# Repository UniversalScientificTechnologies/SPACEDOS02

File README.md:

# SPACEDOS02A - PIN diode dosimeter for manned spacecraft 

SPACEDOS is a miniature and lightweight version of [AIRDOS02](https://github.com/UniversalScientificTechnologies/AIRDOS02) cosmic radiation dosimeter modified for use onboard manned spacecraft.

The device is currently being used onboard ISS. The following pictures show the processed data from the flight. Here is a radiation map, where the [South Atlantic Anomaly](https://en.wikipedia.org/wiki/South_Atlantic_Anomaly) is visible.

The following spectrum is a cumulative sum of all the measured particles during the flight. 

## Technical parameters are as follows:

* Silicon PIN diode detector with 0.22 x 10 x 20 ~ 44 mm³ detection volume
* Measurement environment: atmosphere > 70 kPa
* Measurement endurance: 120 days (4 months of measurement)
* Number of energy channels: 240
* Integration time: Customizable in a wide range from milliseconds to minutes
* Deposited energy range: from 180 keV to 8.5 MeV
* Energy measurement resolution: < 50 keV/channel
* Thermal stability: 1 channel per 12 °C
* Power supply: battery 3.6 V LS 33600
* Power consumption: < 10 mW during measurement, < 120 mW during writing to SD card
* Data storage media: Standard size SDcard, Industry-grade SLC  SD card
* Interface: RS232/UART 3.3V TTL
* Radiation durability: 50 mGy - currently limited by the durability of a storage media
* Dimensions(HxWxL): 60mm x 39mm x 113 mm
* Mass / (including battery): 58/148 g 

## Relevant scientific publications

* [SPACEDOS: AN OPEN-SOURCE PIN DIODE DOSEMETER FOR APPLICATIONS IN SPACE](https://academic.oup.com/rpd/article-abstract/198/9-11/611/6673003?redirectedFrom=fulltext&login=false)
* [SPACEDOS an open-source PIN diode dosimeter for applications in Space](https://indico.ujf.cas.cz/event/2/contributions/27/attachments/25/46/Po-1315-Kakona-774711333.pdf)

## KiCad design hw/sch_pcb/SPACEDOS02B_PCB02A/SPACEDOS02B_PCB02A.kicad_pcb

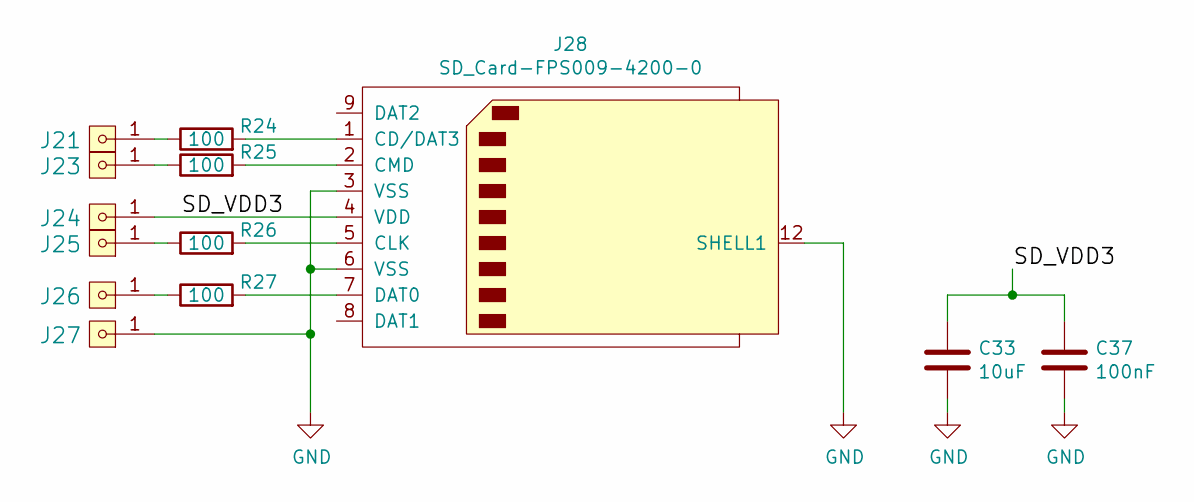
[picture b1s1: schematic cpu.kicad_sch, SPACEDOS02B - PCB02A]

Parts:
C33: 10uF; SMD-0805
C37: 100nF; SMD-0805
J21, J23, J24, J25, J26, J27: HEADER_1x01; Straight_1x01
J28: SD_Card-FPS009-4200-0; FPS009-4200-0
R24, R25, R26, R27: 100; SMD-0805

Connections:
/cpu/SD_VDD3: C33.1, C37.1, J24.1, J28.4 (VDD)
GND: C33.2, C37.2, J27.1, J28.3 (VSS), J28.6 (VSS), J28.12 (SHELL1)
unnamed: J21.1, R24.1
unnamed: J23.1, R25.1
unnamed: J25.1, R26.1
unnamed: J26.1, R27.1
unnamed: J28.1 (CD/DAT3), R24.2
unnamed: J28.2 (CMD), R25.2
unnamed: J28.5 (CLK), R26.2
unnamed: J28.7 (DAT0), R27.2

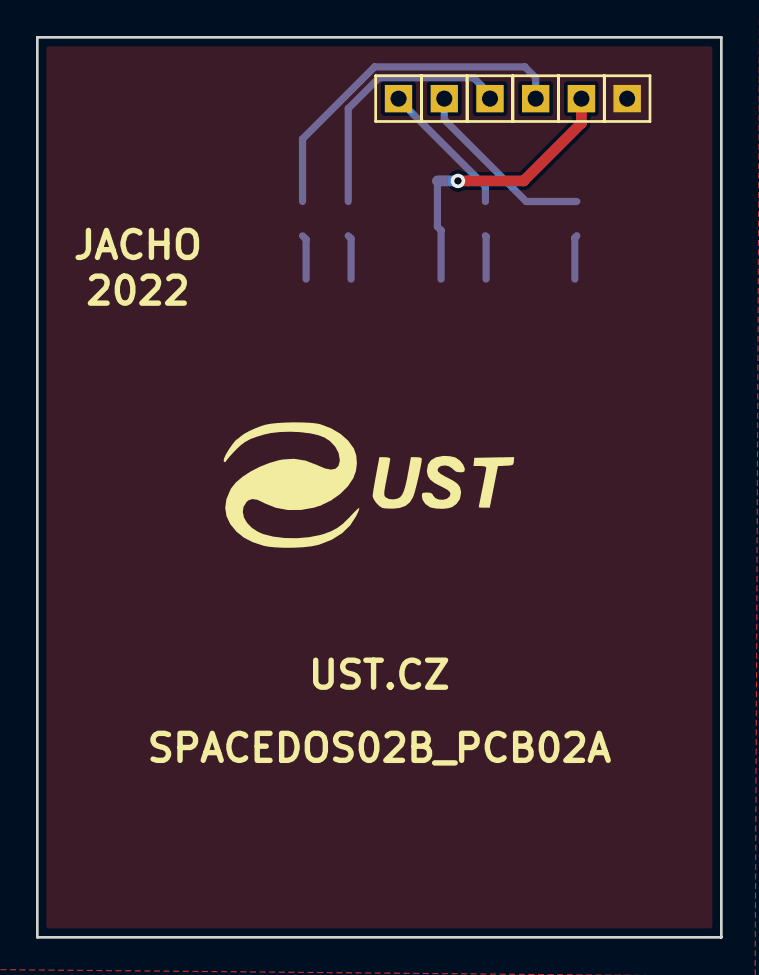
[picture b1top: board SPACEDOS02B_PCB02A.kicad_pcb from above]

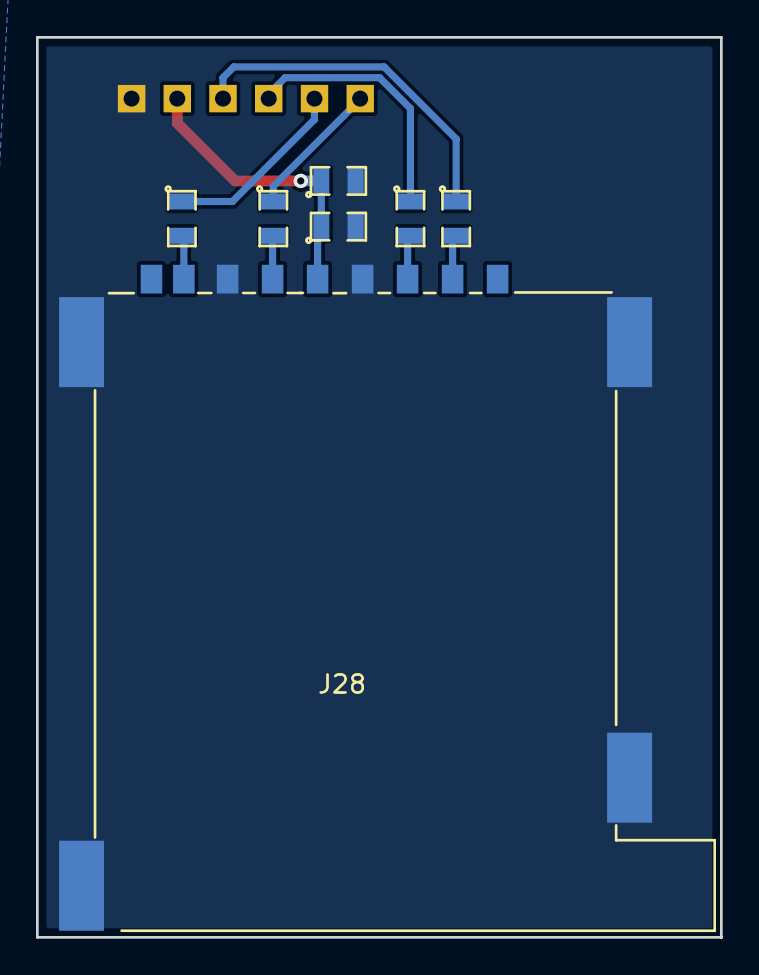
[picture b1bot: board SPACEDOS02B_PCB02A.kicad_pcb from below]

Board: 2 copper layers, 38.0 x 50.0 mm, 13 parts (7 on the bottom side), 10 nets.

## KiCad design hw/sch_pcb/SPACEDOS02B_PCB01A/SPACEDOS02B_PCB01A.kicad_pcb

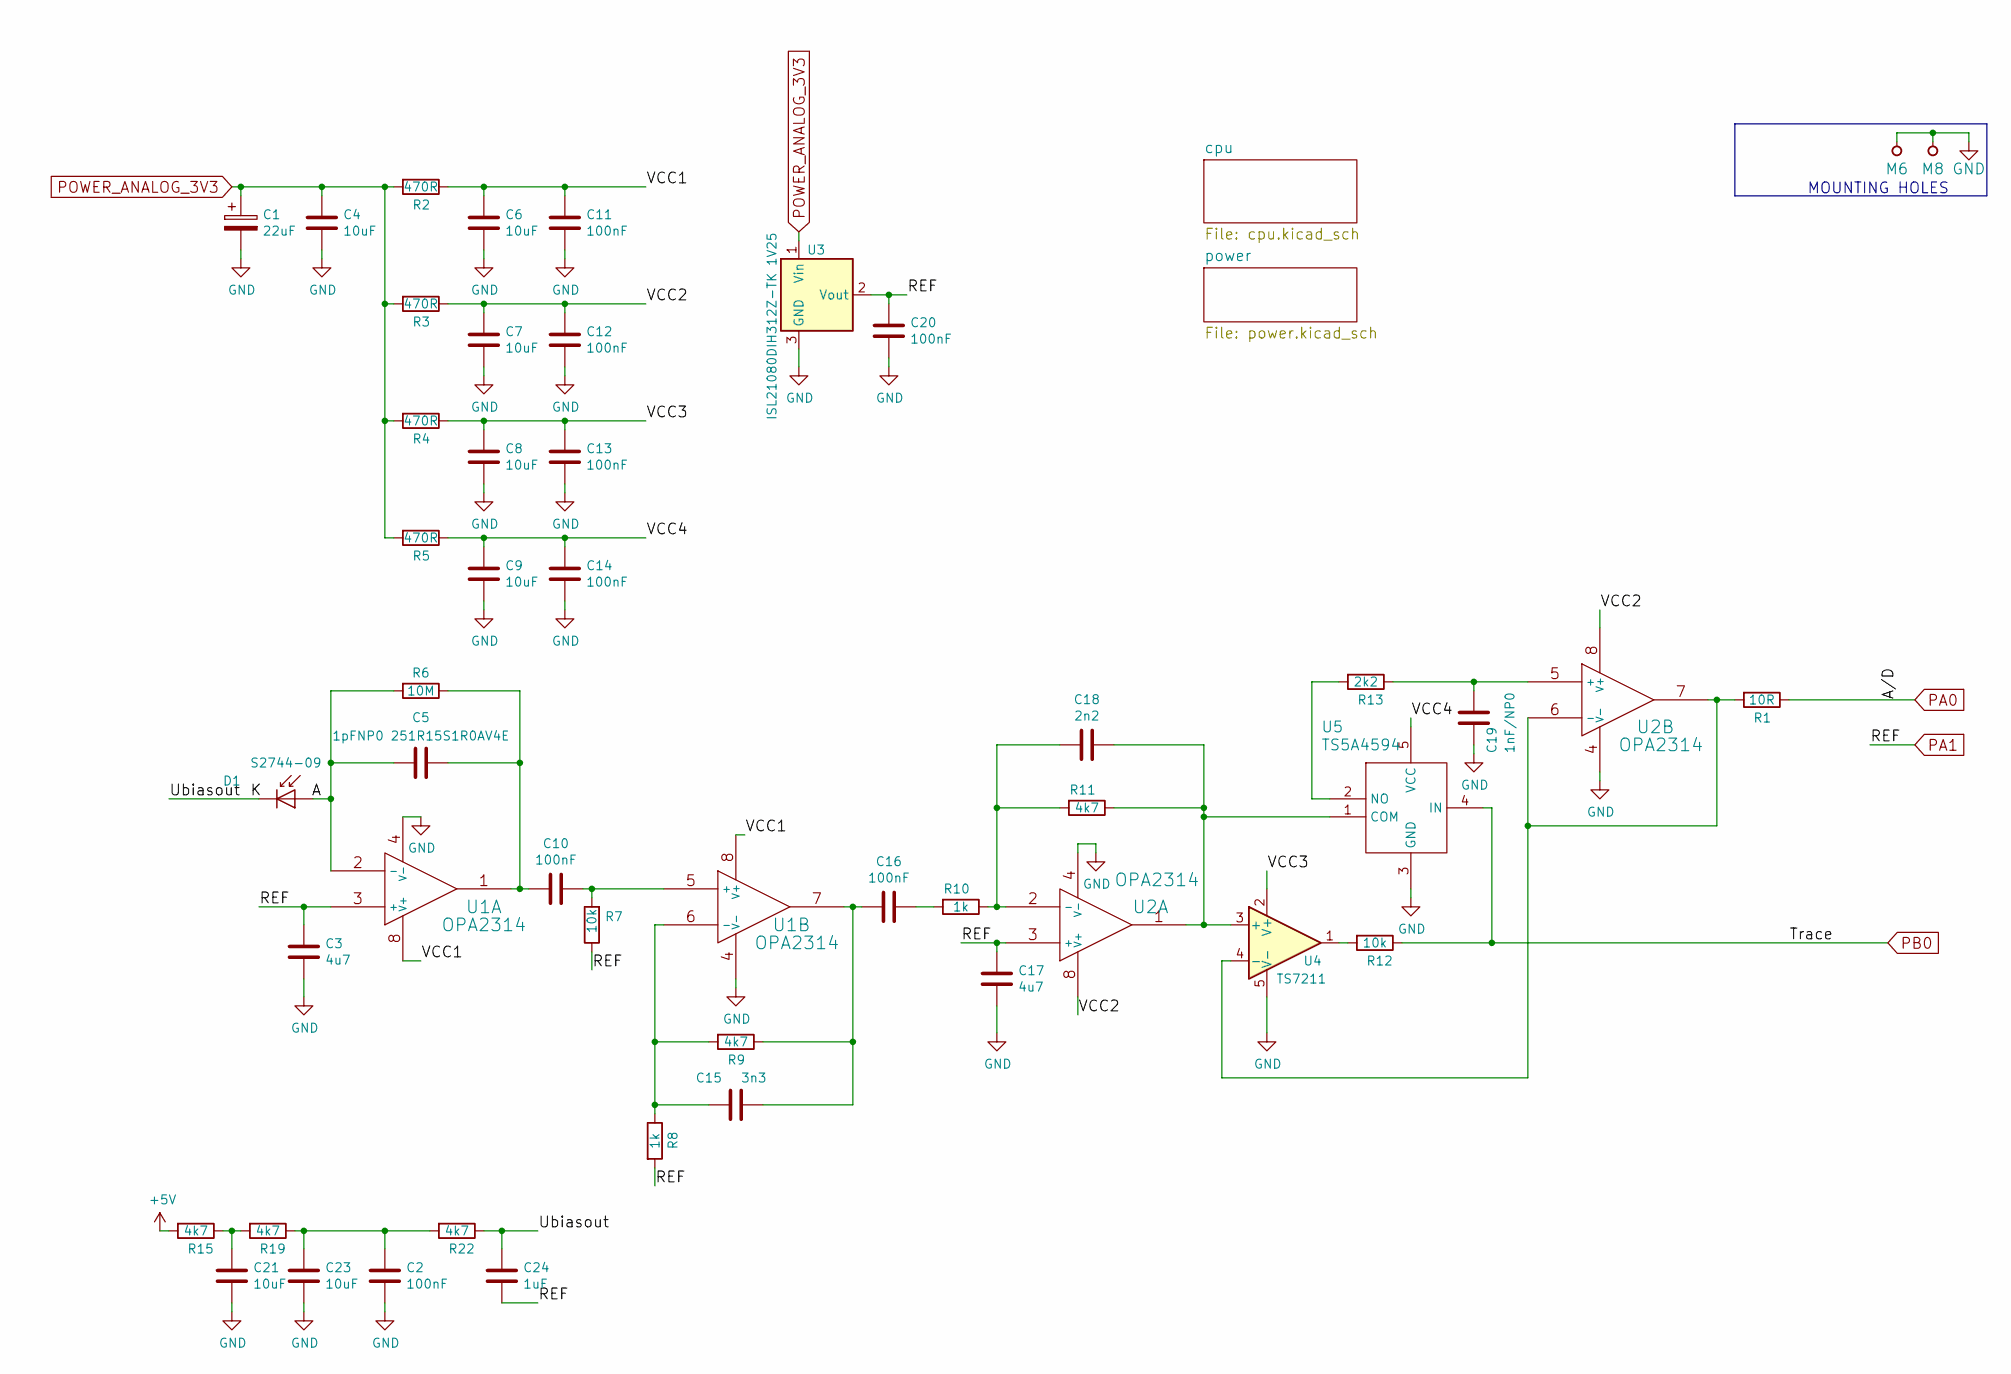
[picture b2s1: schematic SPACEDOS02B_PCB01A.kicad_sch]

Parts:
C1: 22uF; TantalC_SizeC_Reflow
C2, C10, C11, C12, C13, C14, C16, C20: 100nF; SMD-0805
C3, C17: 4u7; SMD-0805
C4, C6, C7, C8, C9, C21, C23: 10uF; SMD-0805
C5: 1pFNP0 251R15S1R0AV4E; SMD-0805
C15: 3n3; SMD-0805
C18: 2n2; SMD-0805
C19: 1nF/NP0; SMD-0805
C24: 1uF; SMD-0805
D1: S2744-09; HAMAMATSU_S2744-09
M6: BMI-S-210-F
M8: BMI-S-210-F; Laird_Technologies_BMI-S-210-F_44.00x30.50mm
R1: 10R; SMD-0805
R2, R3, R4, R5: 470R; SMD-0805
R6: 10M; SMD-0805
R7, R12: 10k; SMD-0805
R8, R10: 1k; SMD-0805
R9, R11, R15, R19, R22: 4k7; SMD-0805
R13: 2k2; SMD-0805
U1, U2: OPA2314; SOIC-8_3.9x4.9mm_Pitch1.27mm
U3: ISL21080DIH312Z-TK 1V25; SOT-23
U4: TS7211; SOT-23-5_HandSoldering
U5: TS5A4594; SOT-23-5_HandSoldering

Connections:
+5V: R15.2; also elsewhere on the board
/A: C5.2, D1.2 (A), R6.2, U1.2 (-)
/K: C24.1, D1.1 (K), R22.1
/VCC1: C6.1, C11.1, R2.1, U1.8 (V+)
/VCC2: C7.1, C12.1, R3.1, U2.8 (V+)
/VCC3: C8.1, C13.1, R4.1, U4.2 (V+)
/VCC4: C9.1, C14.1, R5.1, U5.5 (VCC)
GND: C1.2, C2.2, C3.2, C4.2, C6.2, C7.2, C8.2, C9.2, C11.2, C12.2, C13.2, C14.2, C17.2, C19.2, C20.2, C21.2, C23.2, M6.1, M8.1, U1.4 (V-), U2.4 (V-), U3.3 (GND), U4.5 (V-), U5.3 (GND); also elsewhere on the board
unnamed: C2.1, C23.1, R19.1, R22.2
unnamed: C10.1, R7.2, U1.5 (+)
unnamed: C5.1, C10.2, R6.1, U1.1
unnamed: C15.1, C16.2, R9.1, U1.7
unnamed: C15.2, R8.1, R9.2, U1.6 (-)
unnamed: C16.1, R10.2
unnamed: C18.1, R11.1, U2.1, U4.3 (+), U5.1 (COM)
unnamed: C18.2, R10.1, R11.2, U2.2 (-)
unnamed: C19.1, R13.1, U2.5 (+)
unnamed: C21.1, R15.1, R19.2
unnamed: R1.2, U2.6 (-), U2.7, U4.4 (-)
unnamed: R12.2, U4.1
unnamed: R13.2, U5.2 (NO)
PA0: R1.1; also elsewhere on the board
PA1: C3.1, C17.1, C20.1, C24.2, R7.1, R8.2, U1.3 (+), U2.3 (+), U3.2 (Vout); also elsewhere on the board
PB0: R12.1, U5.4 (IN); also elsewhere on the board
POWER_ANALOG_3V3: C1.1, C4.1, R2.2, R3.2, R4.2, R5.2, U3.1 (Vin); also elsewhere on the board

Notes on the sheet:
MOUNTING HOLES

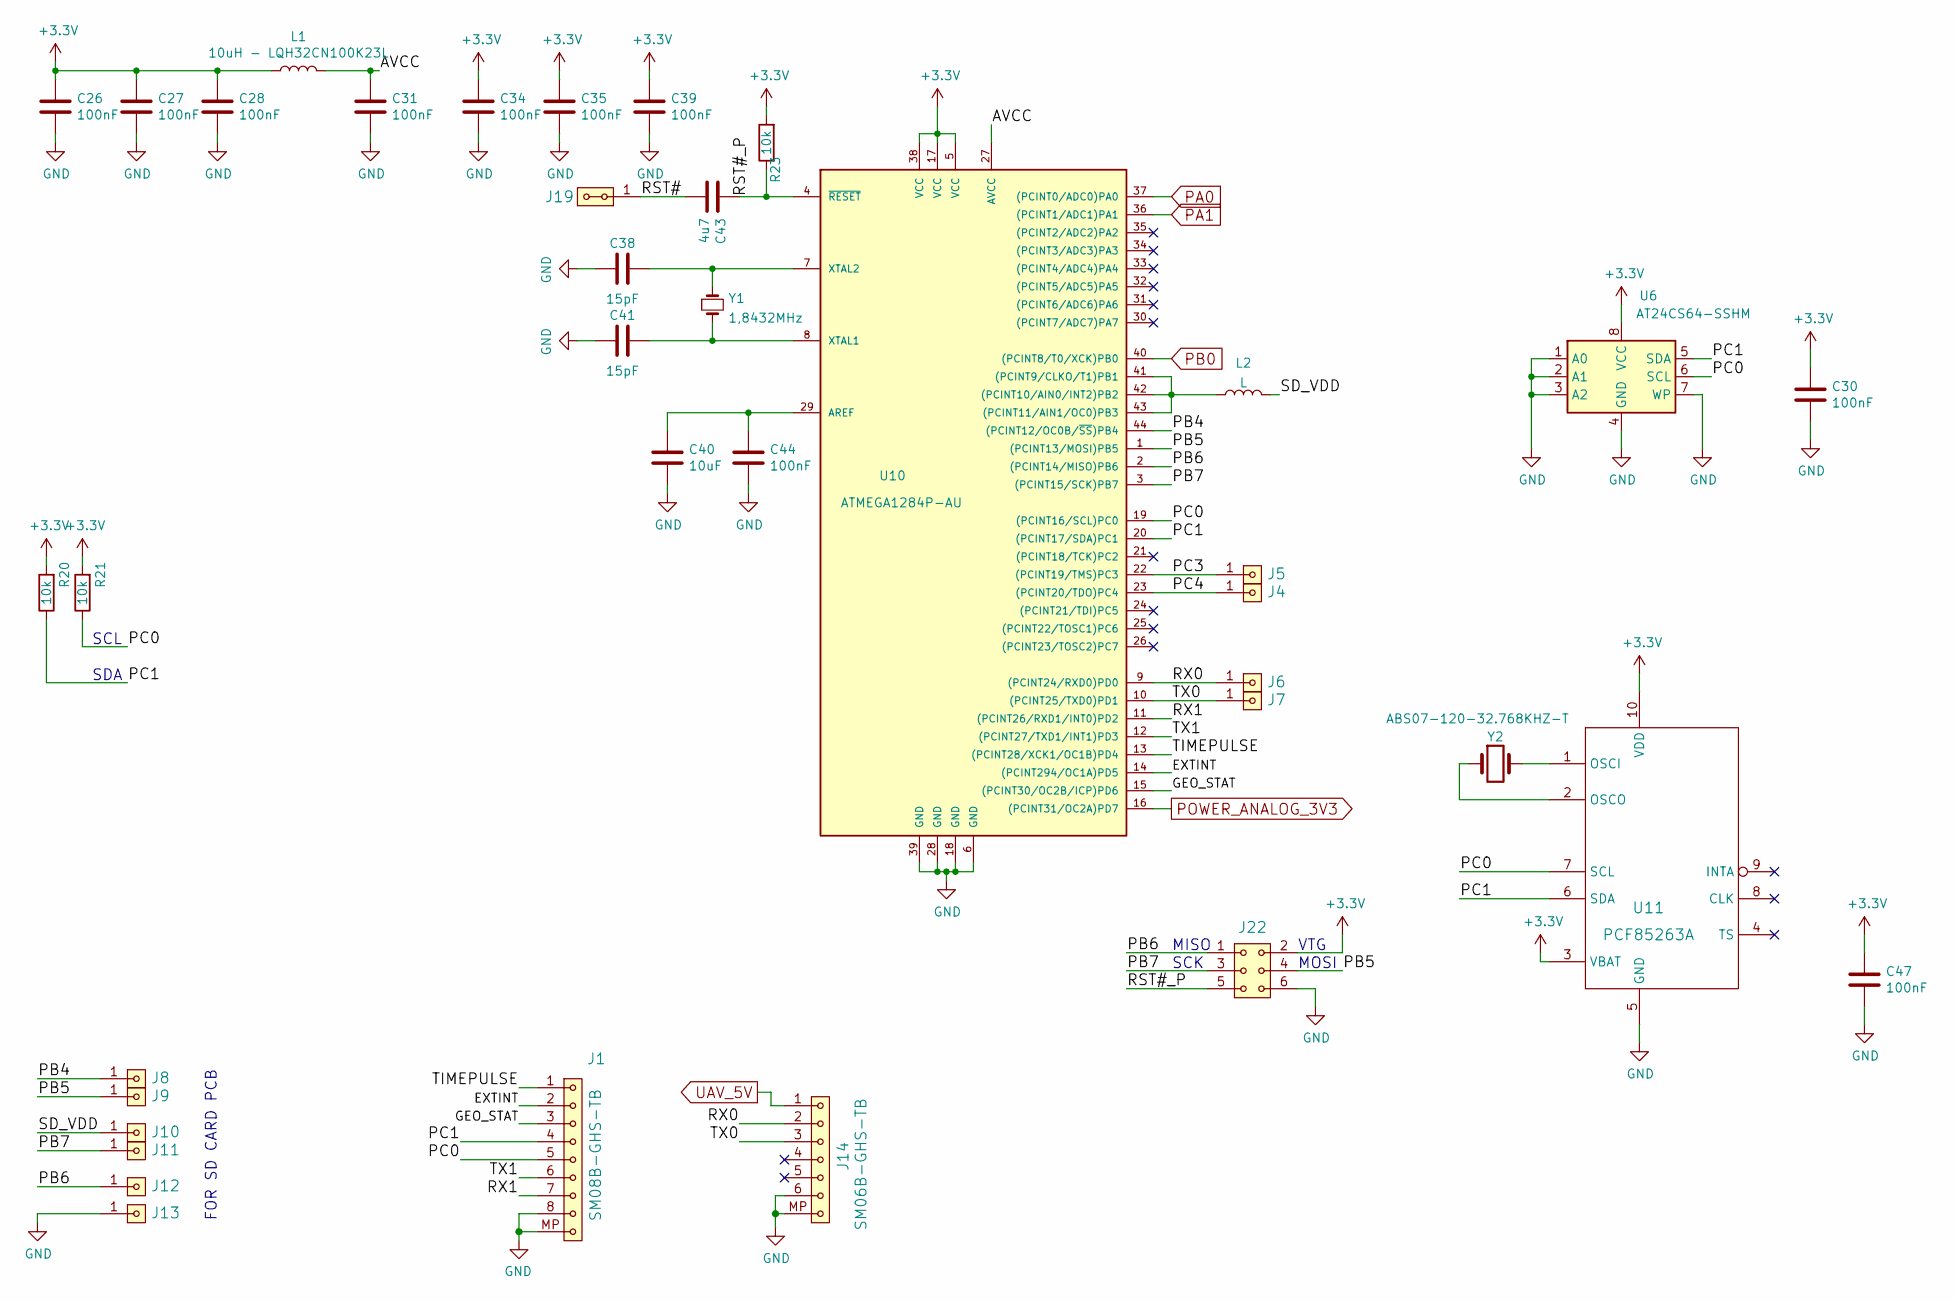
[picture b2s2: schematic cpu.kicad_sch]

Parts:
C26, C27, C28, C30, C31, C34, C35, C39, C44, C47: 100nF; SMD-0805
C38, C41: 15pF; SMD-0805
C40: 10uF; SMD-0805
C43: 4u7; SMD-0805
J1: SM08B-GHS-TB; JST_GH_SM08B-GHS-TB_1x08-1MP_P1.25mm_Horizontal
J4, J5, J6, J7, J8, J9, J10, J11, J12, J13: HEADER_1x01; Straight_1x01
J14: SM06B-GHS-TB; JST_GH_SM06B-GHS-TB_1x06-1MP_P1.25mm_Horizontal
J19: HEADER_2x01_PARALLEL; Straight_2x01
J22: HEADER_2x03; SMD_2x03
L1: 10uH - LQH32CN100K23L; SMD-1210
L2: L
R20, R21, R23: 10k; SMD-0805
U6: AT24CS64-SSHM; SOIC-8_3.9x4.9mm_P1.27mm
U10: ATMEGA1284P-AU; TQFP-44_10x10mm_P0.8mm
U11: PCF85263A; TSSOP-10_3x3mm_Pitch0.5mm
Y1: 1,8432MHz; Crystal_HC49-U_Horizontal
Y2: ABS07-120-32.768KHZ-T; ABS07

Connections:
+3V3: C26.1, C27.1, C28.1, C30.1, C34.1, C35.1, C39.1, C47.1, J22.2, L1.1, R20.2, R21.2, R23.2, U6.8 (VCC), U10.5 (VCC), U10.17 (VCC), U10.38 (VCC), U11.3 (VBAT), U11.10 (VDD); also elsewhere on the board
/cpu/AVCC: C31.1, L1.2, U10.27 (AVCC)
/cpu/EXTINT: J1.2, U10.14 ((PCINT294/OC1A)PD5)
/cpu/GEO_STAT: J1.3, U10.15 ((PCINT30/OC2B/ICP)PD6)
/cpu/PB4: J8.1, U10.44 ((PCINT12/OC0B/~SS)PB4)
/cpu/PB5: J9.1, J22.4, U10.1 ((PCINT13/MOSI)PB5)
/cpu/PB6: J12.1, J22.1, U10.2 ((PCINT14/MISO)PB6)
/cpu/PB7: J11.1, J22.3, U10.3 ((PCINT15/SCK)PB7)
/cpu/PC0: J1.5, R21.1, U6.6 (SCL), U10.19 ((PCINT16/SCL)PC0), U11.7 (SCL)
/cpu/PC1: J1.4, R20.1, U6.5 (SDA), U10.20 ((PCINT17/SDA)PC1), U11.6 (SDA)
/cpu/PC3: J5.1, U10.22 ((PCINT19/TMS)PC3)
/cpu/PC4: J4.1, U10.23 ((PCINT20/TDO)PC4)
/cpu/RST#: C43.2, J19.1, J19.2
/cpu/RST#_P: C43.1, J22.5, R23.1, U10.4 (~RESET)
/cpu/RX0: J6.1, J14.2, U10.9 ((PCINT24/RXD0)PD0)
/cpu/RX1: J1.7, U10.11 ((PCINT26/RXD1/INT0)PD2)
/cpu/SD_VDD: J10.1, L2.2
/cpu/TIMEPULSE: J1.1, U10.13 ((PCINT28/XCK1/OC1B)PD4)
/cpu/TX0: J7.1, J14.3, U10.10 ((PCINT25/TXD0)PD1)
/cpu/TX1: J1.6, U10.12 ((PCINT27/TXD1/INT1)PD3)
GND: C26.2, C27.2, C28.2, C30.2, C31.2, C34.2, C35.2, C38.2, C39.2, C40.2, C41.2, C44.2, C47.2, J1.8, J1.MP, J13.1, J14.6, J14.MP, J22.6, U6.1 (A0), U6.2 (A1), U6.3 (A2), U6.4 (GND), U6.7 (WP), U10.6 (GND), U10.18 (GND), U10.28 (GND), U10.39 (GND), U11.5 (GND); also elsewhere on the board
unnamed: C38.1, U10.7 (XTAL2), Y1.1
unnamed: C40.1, C44.1, U10.29 (AREF)
unnamed: C41.1, U10.8 (XTAL1), Y1.2
unnamed: L2.1, U10.41 ((PCINT9/CLKO/T1)PB1), U10.42 ((PCINT10/AIN0/INT2)PB2), U10.43 ((PCINT11/AIN1/OC0)PB3)
unnamed: U11.1 (OSCI), Y2.2
unnamed: U11.2 (OSCO), Y2.1
PA0: U10.37 ((PCINT0/ADC0)PA0); also elsewhere on the board
PA1: U10.36 ((PCINT1/ADC1)PA1); also elsewhere on the board
PB0: U10.40 ((PCINT8/T0/XCK)PB0); also elsewhere on the board
POWER_ANALOG_3V3: U10.16 ((PCINT31/OC2A)PD7); also elsewhere on the board
UAV_5V: J14.1; also elsewhere on the board

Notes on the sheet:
SCL
FOR SD CARD PCB
SCK
MOSI
SDA
VTG
MISO

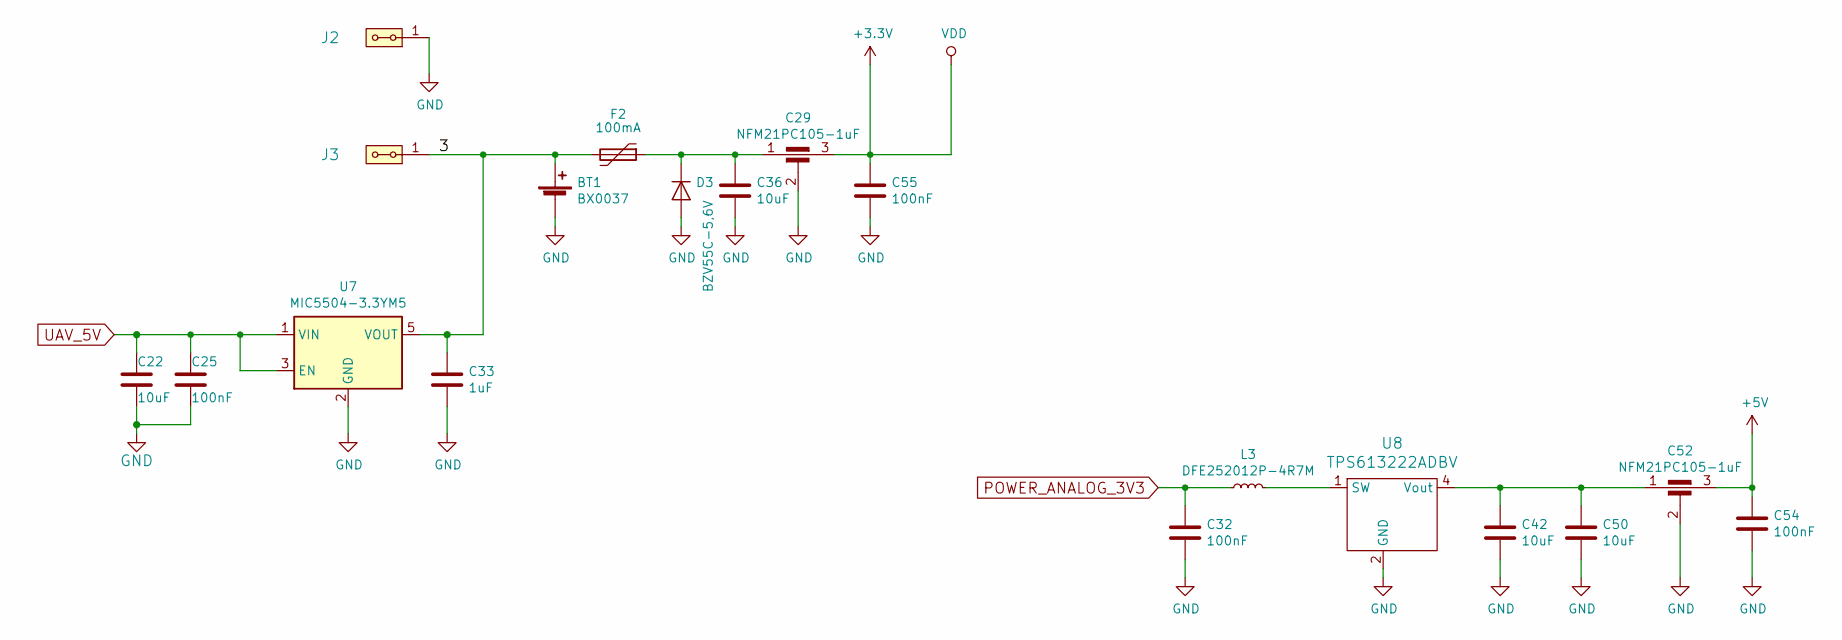
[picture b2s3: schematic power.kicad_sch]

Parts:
BT1: BX0037; BX0037_nez_sroubu
C22, C36, C42, C50: 10uF; SMD-0805
C25: 100nF; SMD-0603
C29, C52: NFM21PC105-1uF; FIR_0805
C32, C54, C55: 100nF; SMD-0805
C33: 1uF; SMD-0603
D3: BZV55C-5,6V; D_MiniMELF
F2: 100mA; SMD-0805
J2, J3: HEADER_2x01_PARALLEL; Straight_1x02
L3: DFE252012P-4R7M; R_0805_2012Metric_Pad1.15x1.40mm_HandSolder
U7: MIC5504-3.3YM5; SOT-23-5
U8: TPS613222ADBV; SOT-23-5

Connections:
+3V3: C29.3, C55.1; also elsewhere on the board
+5V: C52.3, C54.1; also elsewhere on the board
/power/3: BT1.1 (+), C33.1, F2.2, J3.1, J3.2, U7.5 (VOUT)
GND: BT1.2 (-), C22.2, C25.2, C29.2, C32.2, C33.2, C36.2, C42.2, C50.2, C52.2, C54.2, C55.2, D3.2 (A), J2.1, J2.2, U7.2 (GND), U8.2 (GND); also elsewhere on the board
unnamed: C29.1, C36.1, D3.1 (K), F2.1
unnamed: C42.1, C50.1, C52.1, U8.4 (Vout)
unnamed: L3.2, U8.1 (SW)
POWER_ANALOG_3V3: C32.1, L3.1; also elsewhere on the board
UAV_5V: C22.1, C25.1, U7.1 (VIN), U7.3 (EN); also elsewhere on the board

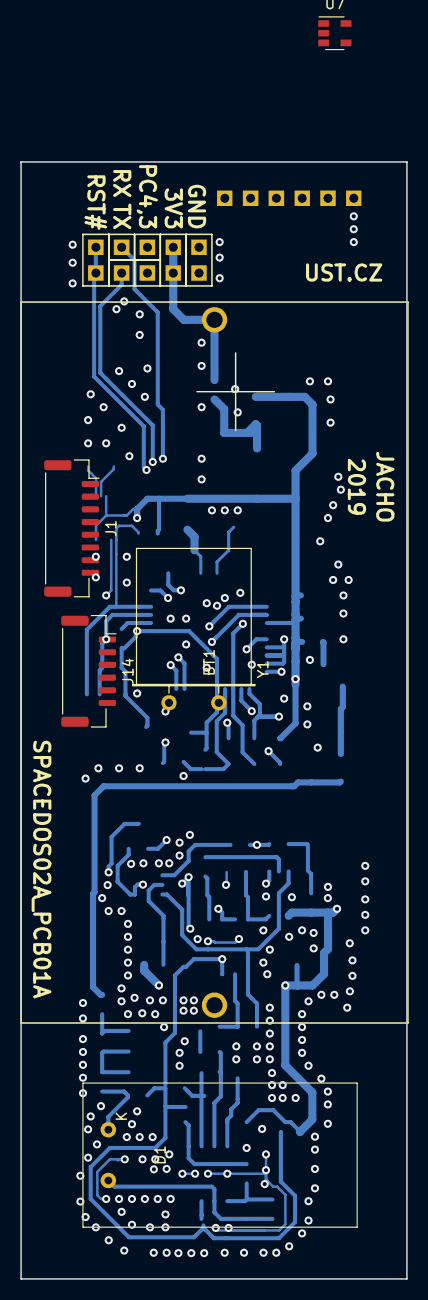
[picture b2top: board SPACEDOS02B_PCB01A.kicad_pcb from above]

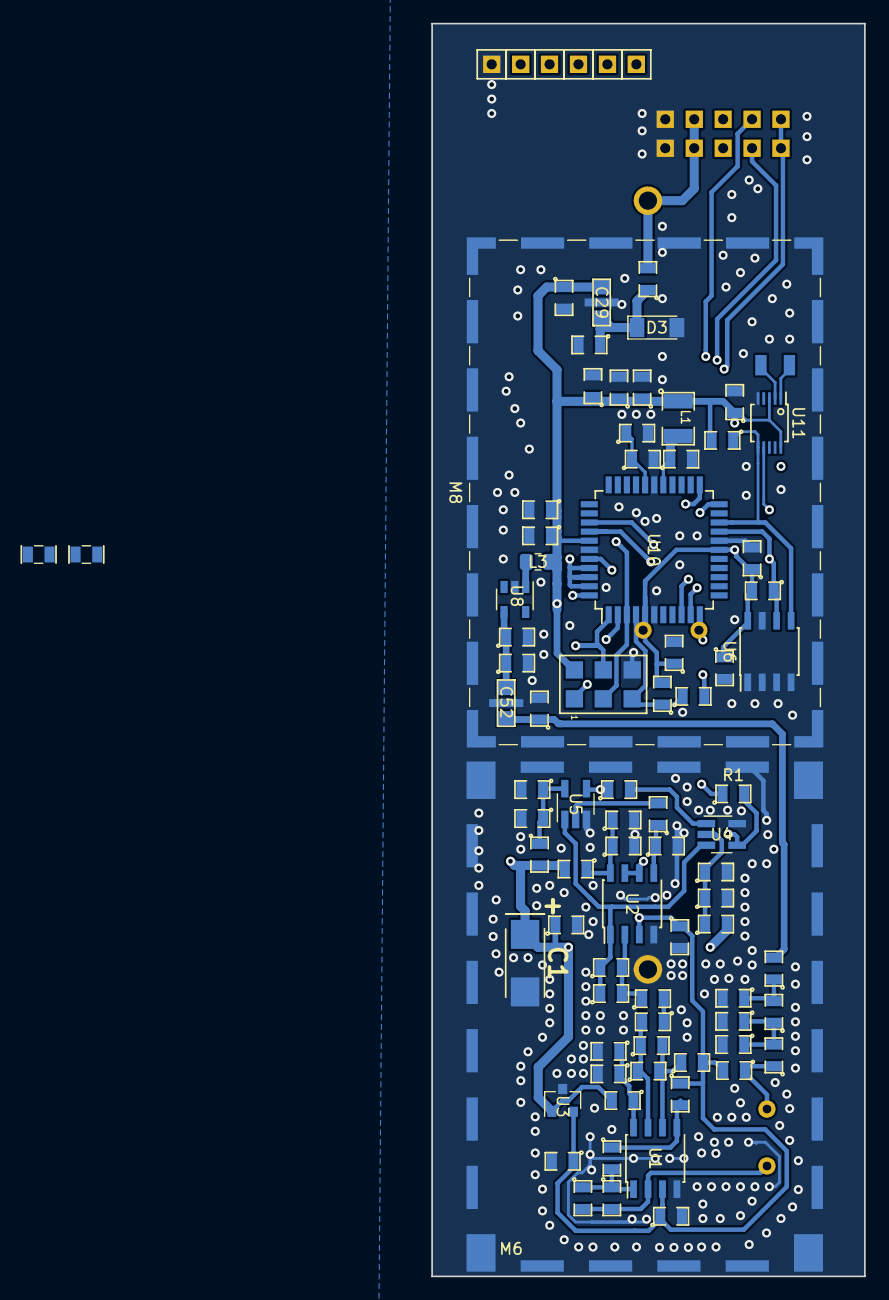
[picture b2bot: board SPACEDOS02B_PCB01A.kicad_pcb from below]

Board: 2 copper layers, 38.0 x 110.0 mm, 100 parts (87 on the bottom side), 55 nets.

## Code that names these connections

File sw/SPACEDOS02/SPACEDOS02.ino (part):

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 
ISP
---
PD0     RX
PD1     TX
RESET#  through 50M capacitor to RST#

SDcard
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
ANALOG
------
+      A0  PA0
-      A1  PA1
RESET  0   PB0

LED
---
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
Startup Delay
-------------
JUMPER  19 PC3    // Selection of delayed start
                  // H = Delayed start
                  // L = Immediate start

                     Mighty 1284p    
                      +---\/---+
           (D 0) PB0 1|        |40 PA0 (AI 0 / D24)
           (D 1) PB1 2|        |39 PA1 (AI 1 / D25)
      INT2 (D 2) PB2 3|        |38 PA2 (AI 2 / D26)
       PWM (D 3) PB3 4|        |37 PA3 (AI 3 / D27)
    PWM/SS (D 4) PB4 5|        |36 PA4 (AI 4 / D28)
      MOSI (D 5) PB5 6|        |35 PA5 (AI 5 / D29)
  PWM/MISO (D 6) PB6 7|        |34 PA6 (AI 6 / D30)
   PWM/SCK (D 7) PB7 8|        |33 PA7 (AI 7 / D31)
                 RST 9|        |32 AREF
                VCC 10|        |31 GND
                GND 11|        |30 AVCC
              XTAL2 12|        |29 PC7 (D 23)
              XTAL1 13|        |28 PC6 (D 22)
      RX0 (D 8) PD0 14|        |27 PC5 (D 21) TDI
      TX0 (D 9) PD1 15|        |26 PC4 (D 20) TDO
RX1/INT0 (D 10) PD2 16|        |25 PC3 (D 19) TMS
TX1/INT1 (D 11) PD3 17|        |24 PC2 (D 18) TCK
     PWM (D 12) PD4 18|        |23 PC1 (D 17) SDA
     PWM (D 13) PD5 19|        |22 PC0 (D 16) SCL
     PWM (D 14) PD6 20|        |21 PD7 (D 15) PWM
                      +--------+
*/

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#include "src/RTCx/RTCx.h"  // Modified version included

#define LED_yellow  23   // PC7
#define RESET       0    // PB0
#define SDpower1    1    // PB1
#define SDpower2    2    // PB2
#define SDpower3    3    // PB3
#define SS          4    // PB4
#define MOSI        5    // PB5
#define MISO        6    // PB6
#define SCK         7    // PB7
#define INT         20   // PC4
#define JUMPER      19   // PC3

#define CHANNELS 512 // number of channels in buffer for histogram, including negative numbers

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
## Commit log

2019-04-26 Edit PCB
2019-05-03 Edit
2019-05-16 Box holder
2019-05-16 zmena vykresu
2019-05-17 uklid, nove parametry
2019-05-19 Zmena modelu
2019-09-05 Vlozena fotka
2020-03-04 Tvorba krabicky
2020-03-04 Uklid nepotrebnych souboru
2020-07-16 before 2nd ISS flight
2020-07-16 flight version
2020-07-16 last test of delayed start before transportation to Moscow
2020-07-18 2nd flight version July 2020 for flight in october 2020
2021-11-02 Images cropped and enhanced.
2021-11-07 Add new submodule with UST titleblock.
2021-11-08 cleanup repository.
2021-11-20 Imrpove the readme.
2021-11-20 Improve the readme.
2021-12-24 Oprava otvíratelnosti schéma.
2021-12-24 #4 add crystal
2021-12-24 Edit schema
2021-12-24 Updated title block updated version of kicad used.
2022-02-18 Set theme jekyll-theme-minimal
2022-03-30 add initial version of UST action
2022-03-30 add initial version of UST action
    Update kicad_outputs.yml
    Update kicad_outputs.yml
    Update kicad_outputs.yml
2022-03-30 Clean repository
2022-03-30 Specify file
2022-03-30 Update actions products
2022-03-30 Update actions
2022-04-16 pridani portfolia
2022-06-29 Update README.md
    Translation update
2022-06-29 Update portfolio.md
    Translation update
2023-02-27 Update README.md
    Improve the parameters list.
2023-09-01 Update README.md
    Correct the detection volume.
2024-01-06 Fix path to images.
2024-01-06 Update portfolio text.
2024-02-17 Update photo metadata.
